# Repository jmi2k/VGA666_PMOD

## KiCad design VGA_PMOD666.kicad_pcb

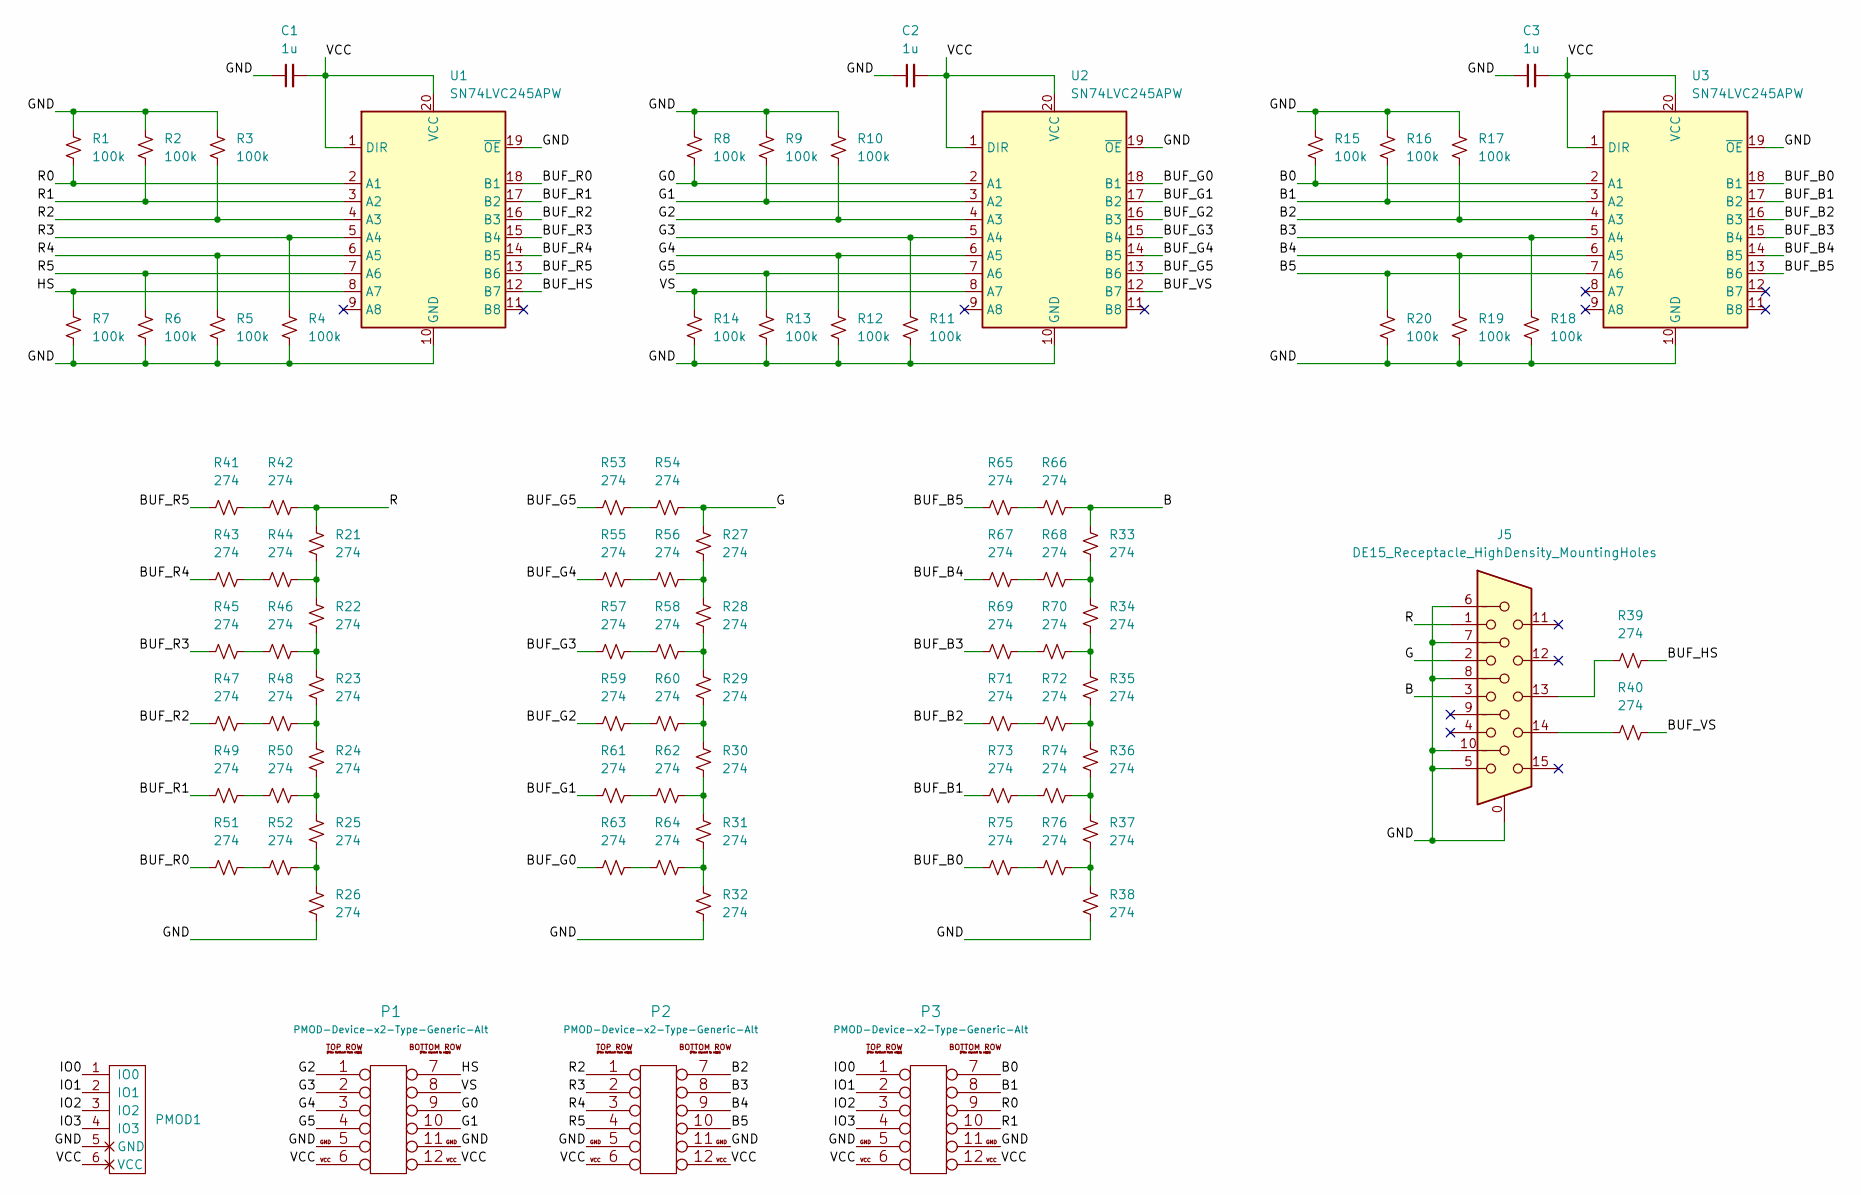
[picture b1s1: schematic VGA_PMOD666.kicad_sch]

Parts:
C1, C2, C3: 1u; C_0402_1005Metric
J5: DE15_Receptacle_HighDensity_MountingHoles; DSUB-15-HD_Female_Horizontal_P2.29x1.98mm_EdgePinOffset3.03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
P1, P2, P3: PMOD-Device-x2-Type-Generic-Alt; pmod_pin_array_6x2
PMOD1: PMOD-Host-x1-GPIO; PinHeader_1x06_P2.54mm_Horizontal
R1, R2, R3, R4, R5, R6, R7, R8, R9, R10, R11, R12, R13, R14, R15, R16, R17, R18, R19, R20: 100k; R_0402_1005Metric
R21, R22, R23, R24, R25, R26, R27, R28, R29, R30, R31, R32, R33, R34, R35, R36, R37, R38, R39, R40, R41, R42, R43, R44, R45, R46, R47, R48, R49, R50, R51, R52, R53, R54, R55, R56, R57, R58, R59, R60, R61, R62, R63, R64, R65, R66, R67, R68, R69, R70, R71, R72, R73, R74, R75, R76: 274; R_0402_1005Metric
U1, U2, U3: SN74LVC245APW; TSSOP-20_4.4x6.5mm_P0.65mm

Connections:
/B: J5.3, R33.2, R66.1
/B0: P3.7, R15.2, U3.2 (A1)
/B1: P3.8, R16.2, U3.3 (A2)
/B2: P2.7, R17.2, U3.4 (A3)
/B3: P2.8, R18.1, U3.5 (A4)
/B4: P2.9, R19.1, U3.6 (A5)
/B5: P2.10, R20.1, U3.7 (A6)
/BUF_B0: R75.2, U3.18 (B1)
/BUF_B1: R73.2, U3.17 (B2)
/BUF_B2: R71.2, U3.16 (B3)
/BUF_B3: R69.2, U3.15 (B4)
/BUF_B4: R67.2, U3.14 (B5)
/BUF_B5: R65.2, U3.13 (B6)
/BUF_G0: R63.2, U2.18 (B1)
/BUF_G1: R61.2, U2.17 (B2)
/BUF_G2: R59.2, U2.16 (B3)
/BUF_G3: R57.2, U2.15 (B4)
/BUF_G4: R55.2, U2.14 (B5)
/BUF_G5: R53.2, U2.13 (B6)
/BUF_HS: R39.2, U1.12 (B7)
/BUF_R0: R51.2, U1.18 (B1)
/BUF_R1: R49.2, U1.17 (B2)
/BUF_R2: R47.2, U1.16 (B3)
/BUF_R3: R45.2, U1.15 (B4)
/BUF_R4: R43.2, U1.14 (B5)
/BUF_R5: R41.2, U1.13 (B6)
/BUF_VS: R40.2, U2.12 (B7)
/G: J5.2, R27.2, R54.1
/G0: P1.9, R8.2, U2.2 (A1)
/G1: P1.10, R9.2, U2.3 (A2)
/G2: P1.1, R10.2, U2.4 (A3)
/G3: P1.2, R11.1, U2.5 (A4)
/G4: P1.3, R12.1, U2.6 (A5)
/G5: P1.4, R13.1, U2.7 (A6)
/GND: C1.1, C2.1, C3.1, J5.0, J5.5, J5.6, J5.7, J5.8, J5.10, P1.5, P1.11, P2.5, P2.11, P3.5, P3.11, PMOD1.5 (GND), R1.1, R2.1, R3.1, R4.2, R5.2, R6.2, R7.2, R8.1, R9.1, R10.1, R11.2, R12.2, R13.2, R14.2, R15.1, R16.1, R17.1, R18.2, R19.2, R20.2, R26.1, R32.1, R38.1, U1.10 (GND), U1.19 (~OE), U2.10 (GND), U2.19 (~OE), U3.10 (GND), U3.19 (~OE)
/HS: P1.7, R7.1, U1.8 (A7)
/IO0: P3.1, PMOD1.1 (IO0)
/IO1: P3.2, PMOD1.2 (IO1)
/IO2: P3.3, PMOD1.3 (IO2)
/IO3: P3.4, PMOD1.4 (IO3)
/R: J5.1, R21.2, R42.1
/R0: P3.9, R1.2, U1.2 (A1)
/R1: P3.10, R2.2, U1.3 (A2)
/R2: P2.1, R3.2, U1.4 (A3)
/R3: P2.2, R4.1, U1.5 (A4)
/R4: P2.3, R5.1, U1.6 (A5)
/R5: P2.4, R6.1, U1.7 (A6)
/VCC: C1.2, C2.2, C3.2, P1.6, P1.12, P2.6, P2.12, P3.6, P3.12, PMOD1.6 (VCC), U1.1 (DIR), U1.20 (VCC), U2.1 (DIR), U2.20 (VCC), U3.1 (DIR), U3.20 (VCC)
/VS: P1.8, R14.1, U2.8 (A7)
unnamed: J5.13, R39.1
unnamed: J5.14, R40.1
unnamed: R21.1, R22.2, R44.1
unnamed: R22.1, R23.2, R46.1
unnamed: R23.1, R24.2, R48.1
unnamed: R24.1, R25.2, R50.1
unnamed: R25.1, R26.2, R52.1
unnamed: R27.1, R28.2, R56.1
unnamed: R28.1, R29.2, R58.1
unnamed: R29.1, R30.2, R60.1
unnamed: R30.1, R31.2, R62.1
unnamed: R31.1, R32.2, R64.1
unnamed: R33.1, R34.2, R68.1
unnamed: R34.1, R35.2, R70.1
unnamed: R35.1, R36.2, R72.1
unnamed: R36.1, R37.2, R74.1
unnamed: R37.1, R38.2, R76.1
unnamed: R41.1, R42.2
unnamed: R43.1, R44.2
unnamed: R45.1, R46.2
unnamed: R47.1, R48.2
unnamed: R49.1, R50.2
unnamed: R51.1, R52.2
unnamed: R53.1, R54.2
unnamed: R55.1, R56.2
unnamed: R57.1, R58.2
unnamed: R59.1, R60.2
unnamed: R61.1, R62.2
unnamed: R63.1, R64.2
unnamed: R65.1, R66.2
unnamed: R67.1, R68.2
unnamed: R69.1, R70.2
unnamed: R71.1, R72.2
unnamed: R73.1, R74.2
unnamed: R75.1, R76.2

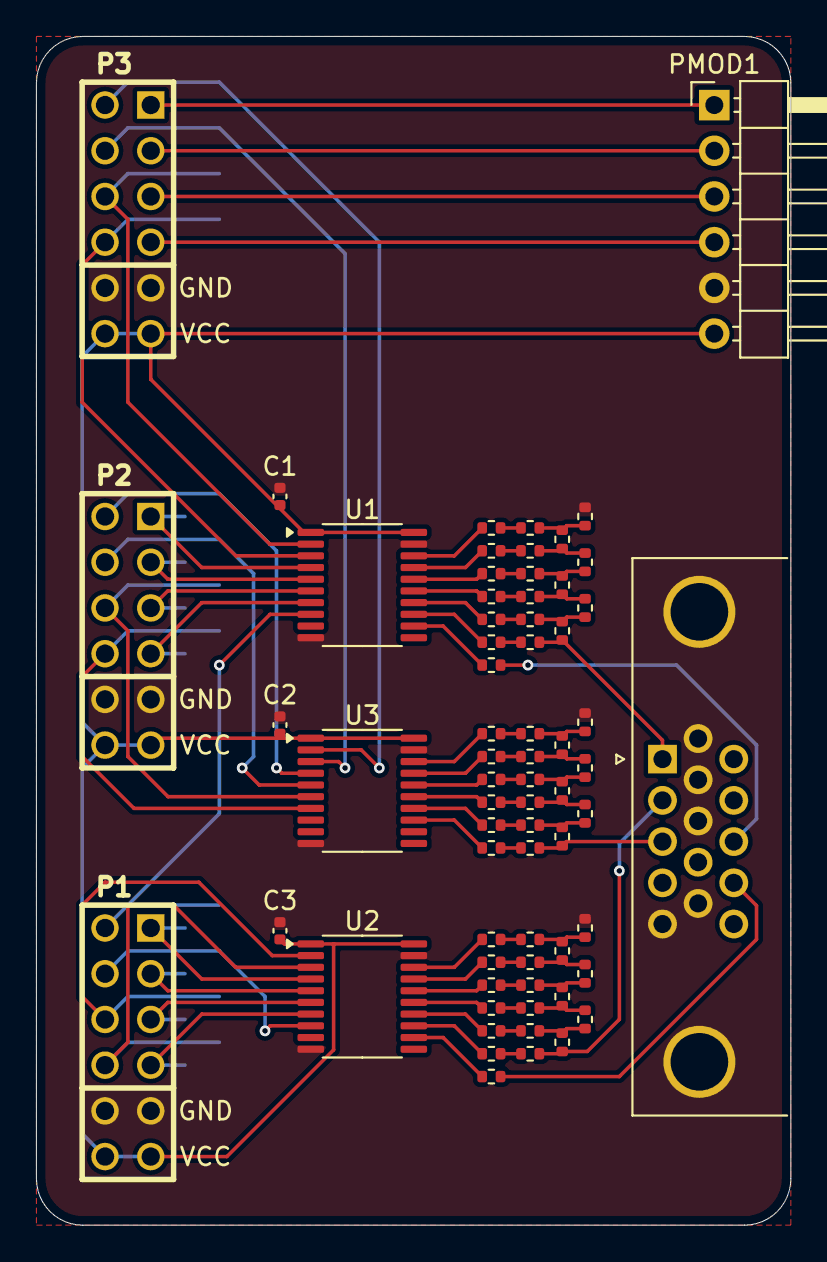
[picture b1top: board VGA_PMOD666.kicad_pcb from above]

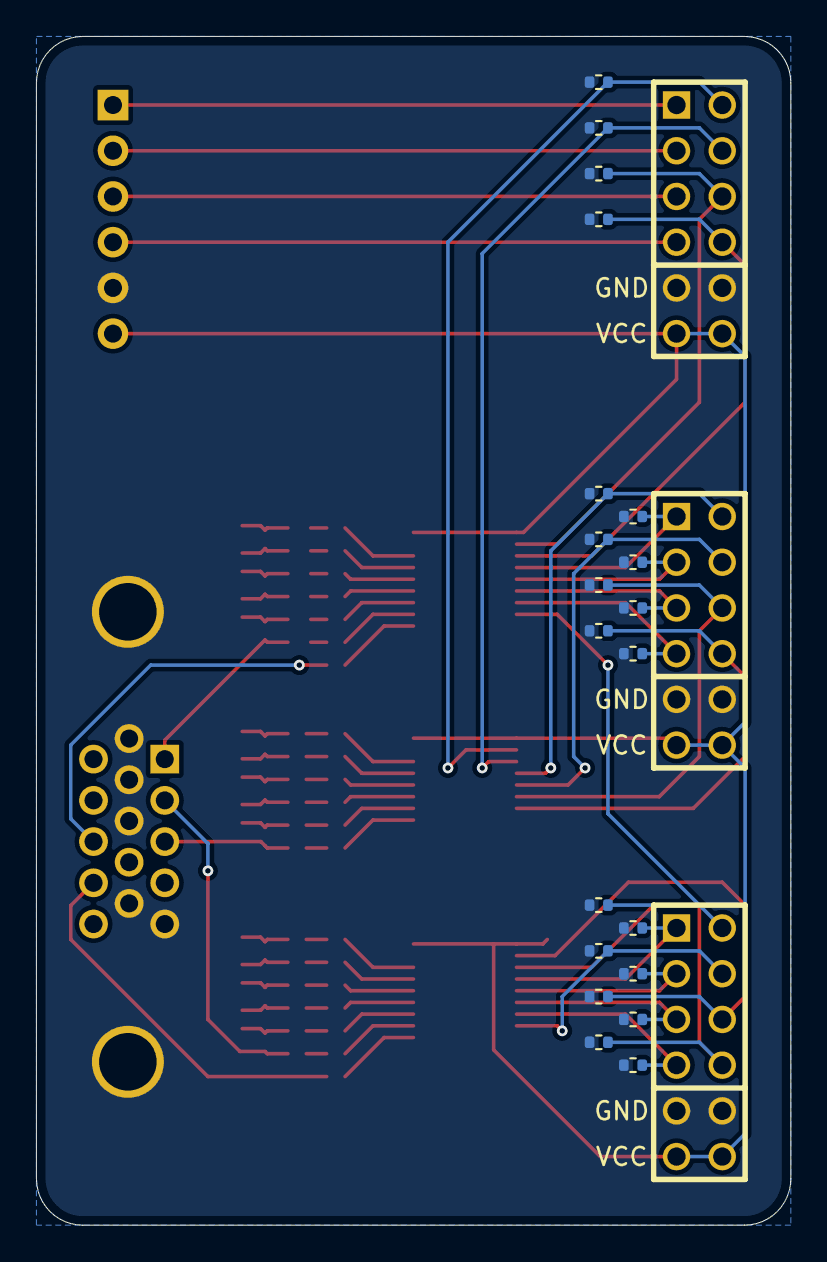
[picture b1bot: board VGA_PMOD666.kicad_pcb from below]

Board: 2 copper layers, 41.9 x 66.0 mm, 87 parts (20 on the bottom side), 84 nets.
